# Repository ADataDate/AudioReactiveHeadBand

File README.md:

# AudioReactiveHeadBand

An audio reactive accessory.

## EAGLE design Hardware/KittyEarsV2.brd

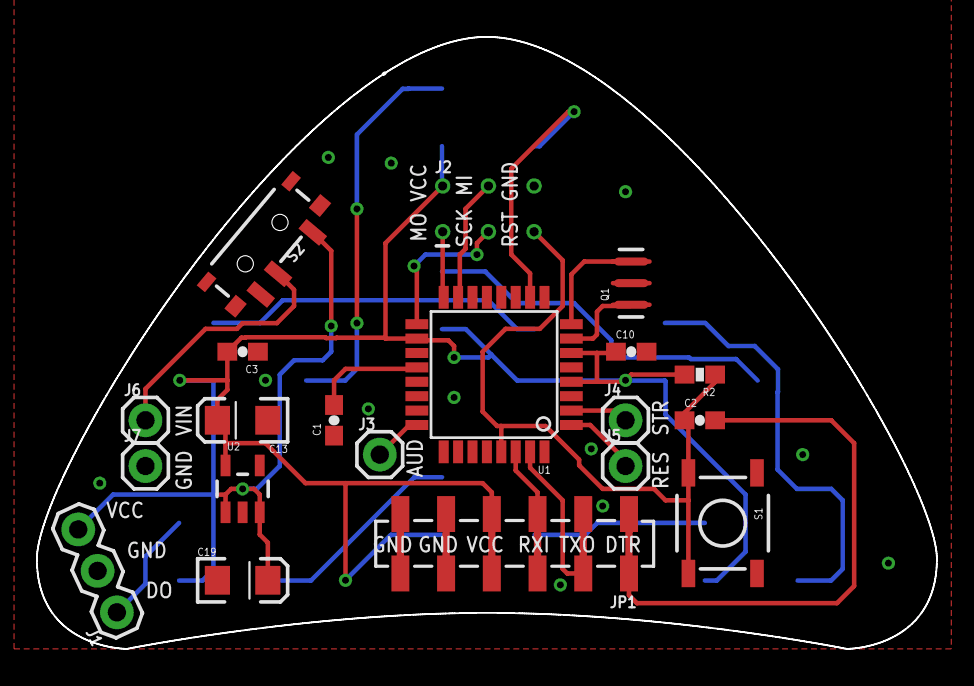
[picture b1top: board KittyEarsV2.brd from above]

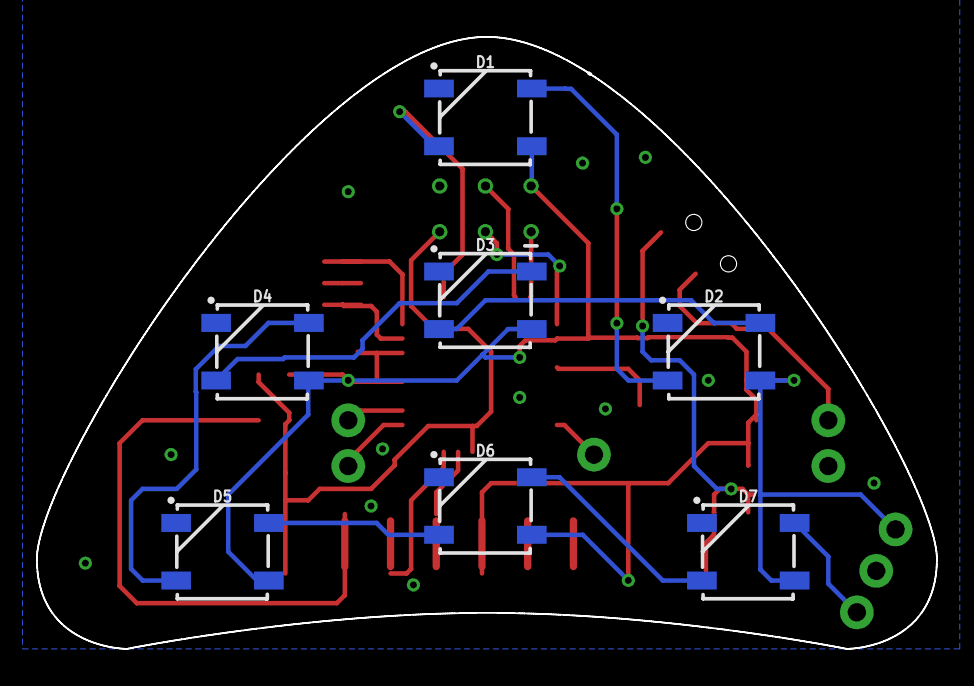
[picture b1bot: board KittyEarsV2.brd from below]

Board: 2 copper layers, 49.9 x 33.9 mm, 28 parts (7 on the bottom side), 25 nets.

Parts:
C1, C2, C3, C10: 0.1uF; 0603-CAP
C13, C19: 10uF; EIA3216
D1, D2, D3, D4, D5, D6, D7: WS2812B
FRAME1: FRAME-LEDGER; CREATIVE_COMMONS
J1: 455-1750-1-ND; 1X03
J2: AVR_SPI_PROG_3X2TESTPOINTS; 2X3_TEST_POINTS
J3, J4, J5, J6, J7: 1X01
JP1: FTDI Basic; 1X06_SMD_STRAIGHT_COMBO
Q1: 8/16/20MHz; RESONATOR-SMD-1:1
R2: 10K; 0603-RES
S1: Reset; TACTILE-SWITCH-SMD-ALT01
S2: SWITCH_SPST_SMD_A
U1: ATMEGA328; TQFP32-08
U2: MIC5205; SOT23-5

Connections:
A1: J3.1, U1.24
AREF: C1.2, U1.20
D3: J5.1, U1.1
D4: J4.1, U1.2
D6: D1.4, U1.10
DO: D7.2, J1.1
DTR: C2.2, JP1.1
GND: C1.1, C3.1, C10.2, C13.C, C19.C, D1.3, D2.3, D3.3, D4.3, D5.3, D6.3, D7.3, J1.2, J2.6, J7.1, JP1.5, JP1.6, Q1.2, S1.1, S1.2, U1.3, U1.5, U1.21, U2.2
MISO: J2.1, U1.16
MOSI: J2.4, U1.15
unnamed: Q1.3, U1.8
unnamed: Q1.1, U1.7
unnamed: D1.2, D2.4
unnamed: D2.2, D3.4
unnamed: D3.2, D4.4
unnamed: D4.2, D5.4
unnamed: D5.2, D6.4
unnamed: D6.2, D7.4
RAW: C19.A, S2.3, U2.1, U2.3
RESET: C2.1, J2.5, R2.1, S1.3, S1.4, U1.29
RXI: JP1.3, U1.30
SCK: J2.3, U1.17
TXO: JP1.2, U1.31
VCC: C3.2, C10.1, C13.A, D1.1, D2.1, D3.1, D4.1, D5.1, D6.1, D7.1, J1.3, J2.2, JP1.4, R2.2, U1.4, U1.6, U1.18, U2.5
VIN: J6.1, S2.2

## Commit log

2018-02-15 code
2018-03-12 adding hardware
2018-04-03 Adding sketch fr new kitty ears
2018-04-03 removing unecessary files and updating sketches
2018-04-03 moving files
2018-04-05 project descr

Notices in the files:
parts and their libraries:
SparkFun-Aesthetics: Licensing: Creative Commons ShareAlike 4.0 International - https://creativecommons.org/licenses/by-sa/4.0
SparkFun-Aesthetics: Released under the Creative Commons Attribution Share-Alike 4.0 License
SparkFun-Aesthetics: https://creativecommons.org/licenses/by-sa/4.0
